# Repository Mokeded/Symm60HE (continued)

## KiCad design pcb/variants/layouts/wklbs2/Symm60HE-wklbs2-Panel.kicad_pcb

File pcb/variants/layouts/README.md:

# Fixed-layout production panels

Each child directory is one self-contained combined electrical project with a
single panel PCB, combined namespaced schematic, captured symbol library and
KiCad project file. Open and manufacture the `*-Panel` project; the retained
`*-Left.kicad_pcb` and `*-Right.kicad_pcb` files are mechanical/migration
inputs rather than separate electrical projects.

The eight directories cover every combination of:

- two 1.5u or three 1u keys on the left bottom row;
- standard or arrow-cluster right bottom row; and
- split or 2u Backspace.

Run `tools/layouts/verify_layout_panels.py` to verify combined schematic/PCB
parity, L/R namespace isolation, FN40HE Hall keepouts, panel dimensions,
mouse-bite rows, tooling holes and fiducials. Matching plate files use the same
directory/layout stem under `plate/`.

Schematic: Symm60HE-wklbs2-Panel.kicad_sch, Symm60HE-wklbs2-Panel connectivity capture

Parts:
L-AML1, L-AML2, L-AML3, L-AML4, L-AML5: SN74LV4051A; AM1_TSSOP-16_4.4x5mm_P0.65mm
L-CL1A, L-CL2A, L-CL3A, L-CL4A, L-CL5A, L-CL6A, L-CL7A, L-CL8A, L-CL9A, L-CL10A, L-CL11A, L-CL12A, L-CL13A, L-CL14A, L-CL15A, L-CL16A, L-CL17A, L-CL18A, L-CL19A, L-CL20A, L-CL21A, L-CL22A, L-CL23A, L-CL24A, L-CL25A, L-CL26A, L-CL28A, L-CL30A, L-CL32A, L-CL33A: 100n; C1_C_0402_1005Metric
L-CL1B, L-CL2B, L-CL3B, L-CL4B, L-CL5B, L-CL6B, L-CL7B, L-CL8B, L-CL9B, L-CL10B, L-CL11B, L-CL12B, L-CL13B, L-CL14B, L-CL15B, L-CL16B, L-CL17B, L-CL18B, L-CL19B, L-CL20B, L-CL21B, L-CL22B, L-CL23B, L-CL24B, L-CL25B, L-CL26B, L-CL28B, L-CL30B, L-CL32B, L-CL33B: 4.7n; C1_C_0402_1005Metric
L-CML1, L-CML2, L-CML3, L-CML4, L-CML5: 100n; C1_C_0402_1005Metric
L-CRGBL1, L-CRGBL2, L-CRGBL3, L-CRGBL4, L-CRGBL5, L-CRGBL6, L-CRGBL7, L-CRGBL8, L-CRGBL9, L-CRGBL10, L-CRGBL11, L-CRGBL12, L-CRGBL13, L-CRGBL14, L-CRGBL15, L-CRGBL16, L-CRGBL17, L-CRGBL18, L-CRGBL19, L-CRGBL20, L-CRGBL21, L-CRGBL22, L-CRGBL23, L-CRGBL24, L-CRGBL25, L-CRGBL26, L-CRGBL27, L-CRGBL29, L-CRGBL30, L-CRGBL31: 100n; C1_C_0402_1005Metric
L-DL1, L-DL2, L-DL3, L-DL4, L-DL5, L-DL6, L-DL7, L-DL8, L-DL9, L-DL10, L-DL11, L-DL12, L-DL13, L-DL14, L-DL15, L-DL16, L-DL17, L-DL18, L-DL19, L-DL20, L-DL21, L-DL22, L-DL23, L-DL24, L-DL25, L-DL26, L-DL27, L-DL29, L-DL30, L-DL31: SK6812MINI-E; SK6812MINI-E_ReverseMount
L-HEL1, L-HEL2, L-HEL3, L-HEL4, L-HEL5, L-HEL6, L-HEL7, L-HEL9, L-HEL10, L-HEL11, L-HEL12, L-HEL13, L-HEL14, L-HEL16, L-HEL17, L-HEL18, L-HEL19, L-HEL20, L-HEL22, L-HEL23, L-HEL24, L-HEL25, L-HEL26: MT9102ET; HE_KEY_1.00u
L-HEL8, L-HEL28, L-HEL30, L-HEL32: MT9102ET; HE_KEY_1.50u
L-HEL15: MT9102ET; HE_KEY_1.75u
L-HEL21, L-HEL33: MT9102ET; HE_KEY_2.25u
L-JL1: FFC_12P; FFC_12P_1.00mm_TopContact
L-RBPL29: 0R_DNP; R3_R_0402_1005Metric_DNP
R-AMR1, R-AMR2, R-AMR3, R-AMR4, R-AMR5: SN74LV4051A; AM1_TSSOP-16_4.4x5mm_P0.65mm
R-CMR1, R-CMR2, R-CMR3, R-CMR4, R-CMR5: 100n; C1_C_0402_1005Metric
R-CR1A, R-CR2A, R-CR4A, R-CR6A, R-CR7A, R-CR8A, R-CR9A, R-CR10A, R-CR11A, R-CR12A, R-CR13A, R-CR14A, R-CR15A, R-CR16A, R-CR17A, R-CR18A, R-CR19A, R-CR20A, R-CR21A, R-CR22A, R-CR23A, R-CR25A, R-CR27A, R-CR28A, R-CR29A, R-CR31A, R-CR33A, R-CR35A, R-CR36A: 100n; C1_C_0402_1005Metric
R-CR1B, R-CR2B, R-CR4B, R-CR6B, R-CR7B, R-CR8B, R-CR9B, R-CR10B, R-CR11B, R-CR12B, R-CR13B, R-CR14B, R-CR15B, R-CR16B, R-CR17B, R-CR18B, R-CR19B, R-CR20B, R-CR21B, R-CR22B, R-CR23B, R-CR25B, R-CR27B, R-CR28B, R-CR29B, R-CR31B, R-CR33B, R-CR35B, R-CR36B: 4.7n; C1_C_0402_1005Metric
R-CRGBR1, R-CRGBR2, R-CRGBR3, R-CRGBR6, R-CRGBR7, R-CRGBR8, R-CRGBR9, R-CRGBR10, R-CRGBR11, R-CRGBR12, R-CRGBR13, R-CRGBR14, R-CRGBR15, R-CRGBR16, R-CRGBR17, R-CRGBR18, R-CRGBR19, R-CRGBR20, R-CRGBR21, R-CRGBR23, R-CRGBR24, R-CRGBR25, R-CRGBR26, R-CRGBR27, R-CRGBR28, R-CRGBR29, R-CRGBR31, R-CRGBR32, R-CRGBR33: 100n; C1_C_0402_1005Metric
R-DR1, R-DR2, R-DR3, R-DR6, R-DR7, R-DR8, R-DR9, R-DR10, R-DR11, R-DR12, R-DR13, R-DR14, R-DR15, R-DR16, R-DR17, R-DR18, R-DR19, R-DR20, R-DR21, R-DR23, R-DR24, R-DR25, R-DR26, R-DR27, R-DR28, R-DR29, R-DR31, R-DR32, R-DR33: SK6812MINI-E; SK6812MINI-E_ReverseMount
R-HER1, R-HER2, R-HER6, R-HER7, R-HER8, R-HER9, R-HER10, R-HER12, R-HER13, R-HER14, R-HER15, R-HER16, R-HER17, R-HER19, R-HER20, R-HER21, R-HER22, R-HER23, R-HER27, R-HER28, R-HER29: MT9102ET; HE_KEY_1.00u
R-HER4: MT9102ET; HE_KEY_2.00u
R-HER11, R-HER31, R-HER33, R-HER35: MT9102ET; HE_KEY_1.50u
R-HER18: MT9102ET; HE_KEY_1.75u
R-HER25, R-HER36: MT9102ET; HE_KEY_2.25u
R-JR1: FFC_12P; FFC_12P_1.00mm_TopContact
R-RBPR5, R-RBPR24, R-RBPR31: 0R_DNP; R3_R_0402_1005Metric_DNP

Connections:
/L/+3V3A: L-AML1.16 (/L/+3V3A), L-AML2.16 (/L/+3V3A), L-AML3.16 (/L/+3V3A), L-AML4.16 (/L/+3V3A), L-AML5.16 (/L/+3V3A), L-CL1A.1 (/L/+3V3A), L-CL2A.1 (/L/+3V3A), L-CL3A.1 (/L/+3V3A), L-CL4A.1 (/L/+3V3A), L-CL5A.1 (/L/+3V3A), L-CL6A.1 (/L/+3V3A), L-CL7A.1 (/L/+3V3A), L-CL8A.1 (/L/+3V3A), L-CL9A.1 (/L/+3V3A), L-CL10A.1 (/L/+3V3A), L-CL11A.1 (/L/+3V3A), L-CL12A.1 (/L/+3V3A), L-CL13A.1 (/L/+3V3A), L-CL14A.1 (/L/+3V3A), L-CL15A.1 (/L/+3V3A), L-CL16A.1 (/L/+3V3A), L-CL17A.1 (/L/+3V3A), L-CL18A.1 (/L/+3V3A), L-CL19A.1 (/L/+3V3A), L-CL20A.1 (/L/+3V3A), L-CL21A.1 (/L/+3V3A), L-CL22A.1 (/L/+3V3A), L-CL23A.1 (/L/+3V3A), L-CL24A.1 (/L/+3V3A), L-CL25A.1 (/L/+3V3A), L-CL26A.1 (/L/+3V3A), L-CL28A.1 (/L/+3V3A), L-CL30A.1 (/L/+3V3A), L-CL32A.1 (/L/+3V3A), L-CL33A.1 (/L/+3V3A), L-CML1.1 (/L/+3V3A), L-CML2.1 (/L/+3V3A), L-CML3.1 (/L/+3V3A), L-CML4.1 (/L/+3V3A), L-CML5.1 (/L/+3V3A), L-HEL1.1 (/L/+3V3A), L-HEL2.1 (/L/+3V3A), L-HEL3.1 (/L/+3V3A), L-HEL4.1 (/L/+3V3A), L-HEL5.1 (/L/+3V3A), L-HEL6.1 (/L/+3V3A), L-HEL7.1 (/L/+3V3A), L-HEL8.1 (/L/+3V3A), L-HEL9.1 (/L/+3V3A), L-HEL10.1 (/L/+3V3A), L-HEL11.1 (/L/+3V3A), L-HEL12.1 (/L/+3V3A), L-HEL13.1 (/L/+3V3A), L-HEL14.1 (/L/+3V3A), L-HEL15.1 (/L/+3V3A), L-HEL16.1 (/L/+3V3A), L-HEL17.1 (/L/+3V3A), L-HEL18.1 (/L/+3V3A), L-HEL19.1 (/L/+3V3A), L-HEL20.1 (/L/+3V3A), L-HEL21.1 (/L/+3V3A), L-HEL22.1 (/L/+3V3A), L-HEL23.1 (/L/+3V3A), L-HEL24.1 (/L/+3V3A), L-HEL25.1 (/L/+3V3A), L-HEL26.1 (/L/+3V3A), L-HEL28.1 (/L/+3V3A), L-HEL30.1 (/L/+3V3A), L-HEL32.1 (/L/+3V3A), L-HEL33.1 (/L/+3V3A), L-JL1.12 (/L/+3V3A)
/L/ADC_L1: L-AML1.3 (/L/ADC_L1), L-JL1.6 (/L/ADC_L1)
/L/ADC_L2: L-AML2.3 (/L/ADC_L2), L-JL1.4 (/L/ADC_L2)
/L/ADC_L3: L-AML3.3 (/L/ADC_L3), L-JL1.2 (/L/ADC_L3)
/L/ADC_L4: L-AML4.3 (/L/ADC_L4), L-JL1.1 (/L/ADC_L4)
/L/ADC_L5: L-AML5.3 (/L/ADC_L5), L-JL1.11 (/L/ADC_L5)
/L/GND: L-AML1.6 (/L/GND), L-AML1.7 (/L/GND), L-AML1.8 (/L/GND), L-AML2.4 (/L/GND), L-AML2.6 (/L/GND), L-AML2.7 (/L/GND), L-AML2.8 (/L/GND), L-AML3.6 (/L/GND), L-AML3.7 (/L/GND), L-AML3.8 (/L/GND), L-AML4.2 (/L/GND), L-AML4.4 (/L/GND), L-AML4.6 (/L/GND), L-AML4.7 (/L/GND), L-AML4.8 (/L/GND), L-AML4.13 (/L/GND), L-AML4.14 (/L/GND), L-AML5.6 (/L/GND), L-AML5.7 (/L/GND), L-AML5.8 (/L/GND), L-AML5.12 (/L/GND), L-AML5.13 (/L/GND), L-AML5.14 (/L/GND), L-AML5.15 (/L/GND), L-CL1A.2 (/L/GND), L-CL1B.2 (/L/GND), L-CL2A.2 (/L/GND), L-CL2B.2 (/L/GND), L-CL3A.2 (/L/GND), L-CL3B.2 (/L/GND), L-CL4A.2 (/L/GND), L-CL4B.2 (/L/GND), L-CL5A.2 (/L/GND), L-CL5B.2 (/L/GND), L-CL6A.2 (/L/GND), L-CL6B.2 (/L/GND), L-CL7A.2 (/L/GND), L-CL7B.2 (/L/GND), L-CL8A.2 (/L/GND), L-CL8B.2 (/L/GND), L-CL9A.2 (/L/GND), L-CL9B.2 (/L/GND), L-CL10A.2 (/L/GND), L-CL10B.2 (/L/GND), L-CL11A.2 (/L/GND), L-CL11B.2 (/L/GND), L-CL12A.2 (/L/GND), L-CL12B.2 (/L/GND), L-CL13A.2 (/L/GND), L-CL13B.2 (/L/GND), L-CL14A.2 (/L/GND), L-CL14B.2 (/L/GND), L-CL15A.2 (/L/GND), L-CL15B.2 (/L/GND), L-CL16A.2 (/L/GND), L-CL16B.2 (/L/GND), L-CL17A.2 (/L/GND), L-CL17B.2 (/L/GND), L-CL18A.2 (/L/GND), L-CL18B.2 (/L/GND), L-CL19A.2 (/L/GND), L-CL19B.2 (/L/GND), L-CL20A.2 (/L/GND), L-CL20B.2 (/L/GND), L-CL21A.2 (/L/GND), L-CL21B.2 (/L/GND), L-CL22A.2 (/L/GND), L-CL22B.2 (/L/GND), L-CL23A.2 (/L/GND), L-CL23B.2 (/L/GND), L-CL24A.2 (/L/GND), L-CL24B.2 (/L/GND), L-CL25A.2 (/L/GND), L-CL25B.2 (/L/GND), L-CL26A.2 (/L/GND), L-CL26B.2 (/L/GND), L-CL28A.2 (/L/GND), L-CL28B.2 (/L/GND), L-CL30A.2 (/L/GND), L-CL30B.2 (/L/GND), L-CL32A.2 (/L/GND), L-CL32B.2 (/L/GND), L-CL33A.2 (/L/GND), L-CL33B.2 (/L/GND), L-CML1.2 (/L/GND), L-CML2.2 (/L/GND), L-CML3.2 (/L/GND), L-CML4.2 (/L/GND), L-CML5.2 (/L/GND), L-CRGBL1.2 (/L/GND), L-CRGBL2.2 (/L/GND), L-CRGBL3.2 (/L/GND), L-CRGBL4.2 (/L/GND), L-CRGBL5.2 (/L/GND), L-CRGBL6.2 (/L/GND), L-CRGBL7.2 (/L/GND), L-CRGBL8.2 (/L/GND), L-CRGBL9.2 (/L/GND), L-CRGBL10.2 (/L/GND), L-CRGBL11.2 (/L/GND), L-CRGBL12.2 (/L/GND), L-CRGBL13.2 (/L/GND)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
/L/HE_L01: L-AML1.12 (/L/HE_L01), L-CL1B.1 (/L/HE_L01), L-HEL1.3 (/L/HE_L01)
/L/HE_L02: L-AML1.13 (/L/HE_L02), L-CL2B.1 (/L/HE_L02), L-HEL2.3 (/L/HE_L02)
/L/HE_L03: L-AML1.14 (/L/HE_L03), L-CL3B.1 (/L/HE_L03), L-HEL3.3 (/L/HE_L03)
/L/HE_L04: L-AML1.15 (/L/HE_L04), L-CL4B.1 (/L/HE_L04), L-HEL4.3 (/L/HE_L04)
/L/HE_L05: L-AML2.12 (/L/HE_L05), L-CL5B.1 (/L/HE_L05), L-HEL5.3 (/L/HE_L05)
/L/HE_L06: L-AML2.13 (/L/HE_L06), L-CL6B.1 (/L/HE_L06), L-HEL6.3 (/L/HE_L06)
/L/HE_L07: L-AML2.14 (/L/HE_L07), L-CL7B.1 (/L/HE_L07), L-HEL7.3 (/L/HE_L07)
/L/HE_L08: L-AML1.5 (/L/HE_L08), L-CL8B.1 (/L/HE_L08), L-HEL8.3 (/L/HE_L08)
/L/HE_L09: L-AML1.4 (/L/HE_L09), L-CL9B.1 (/L/HE_L09), L-HEL9.3 (/L/HE_L09)
/L/HE_L10: L-AML1.2 (/L/HE_L10), L-CL10B.1 (/L/HE_L10), L-HEL10.3 (/L/HE_L10)
/L/HE_L11: L-AML1.1 (/L/HE_L11), L-CL11B.1 (/L/HE_L11), L-HEL11.3 (/L/HE_L11)
/L/HE_L12: L-AML2.5 (/L/HE_L12), L-CL12B.1 (/L/HE_L12), L-HEL12.3 (/L/HE_L12)
/L/HE_L13: L-AML2.2 (/L/HE_L13), L-CL13B.1 (/L/HE_L13), L-HEL13.3 (/L/HE_L13)
/L/HE_L14: L-AML2.1 (/L/HE_L14), L-CL14B.1 (/L/HE_L14), L-HEL14.3 (/L/HE_L14)
/L/HE_L15: L-AML3.12 (/L/HE_L15), L-CL15B.1 (/L/HE_L15), L-HEL15.3 (/L/HE_L15)
/L/HE_L16: L-AML3.13 (/L/HE_L16), L-CL16B.1 (/L/HE_L16), L-HEL16.3 (/L/HE_L16)
/L/HE_L17: L-AML3.14 (/L/HE_L17), L-CL17B.1 (/L/HE_L17), L-HEL17.3 (/L/HE_L17)
/L/HE_L18: L-AML3.15 (/L/HE_L18), L-CL18B.1 (/L/HE_L18), L-HEL18.3 (/L/HE_L18)
/L/HE_L19: L-AML4.12 (/L/HE_L19), L-CL19B.1 (/L/HE_L19), L-HEL19.3 (/L/HE_L19)
/L/HE_L20: L-AML4.15 (/L/HE_L20), L-CL20B.1 (/L/HE_L20), L-HEL20.3 (/L/HE_L20)
/L/HE_L21: L-AML3.5 (/L/HE_L21), L-CL21B.1 (/L/HE_L21), L-HEL21.3 (/L/HE_L21)
/L/HE_L22: L-AML3.4 (/L/HE_L22), L-CL22B.1 (/L/HE_L22), L-HEL22.3 (/L/HE_L22)
/L/HE_L23: L-AML3.2 (/L/HE_L23), L-CL23B.1 (/L/HE_L23), L-HEL23.3 (/L/HE_L23)
/L/HE_L24: L-AML3.1 (/L/HE_L24), L-CL24B.1 (/L/HE_L24), L-HEL24.3 (/L/HE_L24)
/L/HE_L25: L-AML4.5 (/L/HE_L25), L-CL25B.1 (/L/HE_L25), L-HEL25.3 (/L/HE_L25)
/L/HE_L26: L-AML4.1 (/L/HE_L26), L-CL26B.1 (/L/HE_L26), L-HEL26.3 (/L/HE_L26)
/L/HE_L30: L-AML5.2 (/L/HE_L30), L-CL32B.1 (/L/HE_L30), L-HEL32.3 (/L/HE_L30)
/L/HE_L31: L-AML5.1 (/L/HE_L31), L-CL33B.1 (/L/HE_L31), L-HEL33.3 (/L/HE_L31)
/L/HE_L32: L-AML5.4 (/L/HE_L32), L-CL28B.1 (/L/HE_L32), L-HEL28.3 (/L/HE_L32)
/L/HE_L33: L-AML5.5 (/L/HE_L33), L-CL30B.1 (/L/HE_L33), L-HEL30.3 (/L/HE_L33)
/L/MUX_A0: L-AML1.11 (/L/MUX_A0), L-AML2.11 (/L/MUX_A0), L-AML3.11 (/L/MUX_A0), L-AML4.11 (/L/MUX_A0), L-AML5.11 (/L/MUX_A0), L-JL1.10 (/L/MUX_A0)
/L/MUX_A1: L-AML1.10 (/L/MUX_A1), L-AML2.10 (/L/MUX_A1), L-AML3.10 (/L/MUX_A1), L-AML4.10 (/L/MUX_A1), L-AML5.10 (/L/MUX_A1), L-JL1.9 (/L/MUX_A1)
/L/MUX_A2: L-AML1.9 (/L/MUX_A2), L-AML2.9 (/L/MUX_A2), L-AML3.9 (/L/MUX_A2), L-AML4.9 (/L/MUX_A2), L-AML5.9 (/L/MUX_A2), L-JL1.8 (/L/MUX_A2)
/L/RGB_L: L-DL1.2 (/L/RGB_L), L-JL1.3 (/L/RGB_L)
/L/RGB_L_01: L-DL1.4 (/L/RGB_L_01), L-DL2.2 (/L/RGB_L_01)
/L/RGB_L_02: L-DL2.4 (/L/RGB_L_02), L-DL3.2 (/L/RGB_L_02)
/L/RGB_L_03: L-DL3.4 (/L/RGB_L_03), L-DL4.2 (/L/RGB_L_03)
/L/RGB_L_04: L-DL4.4 (/L/RGB_L_04), L-DL5.2 (/L/RGB_L_04)
/L/RGB_L_05: L-DL5.4 (/L/RGB_L_05), L-DL6.2 (/L/RGB_L_05)
/L/RGB_L_06: L-DL6.4 (/L/RGB_L_06), L-DL7.2 (/L/RGB_L_06)
/L/RGB_L_07: L-DL7.4 (/L/RGB_L_07), L-DL8.2 (/L/RGB_L_07)
/L/RGB_L_08: L-DL8.4 (/L/RGB_L_08), L-DL9.2 (/L/RGB_L_08)
/L/RGB_L_09: L-DL9.4 (/L/RGB_L_09), L-DL10.2 (/L/RGB_L_09)
/L/RGB_L_10: L-DL10.4 (/L/RGB_L_10), L-DL11.2 (/L/RGB_L_10)
/L/RGB_L_11: L-DL11.4 (/L/RGB_L_11), L-DL12.2 (/L/RGB_L_11)
/L/RGB_L_12: L-DL12.4 (/L/RGB_L_12), L-DL13.2 (/L/RGB_L_12)
/L/RGB_L_13: L-DL13.4 (/L/RGB_L_13), L-DL14.2 (/L/RGB_L_13)
/L/RGB_L_14: L-DL14.4 (/L/RGB_L_14), L-DL15.2 (/L/RGB_L_14)
/L/RGB_L_15: L-DL15.4 (/L/RGB_L_15), L-DL16.2 (/L/RGB_L_15)
/L/RGB_L_16: L-DL16.4 (/L/RGB_L_16), L-DL17.2 (/L/RGB_L_16)
/L/RGB_L_17: L-DL17.4 (/L/RGB_L_17), L-DL18.2 (/L/RGB_L_17)
/L/RGB_L_18: L-DL18.4 (/L/RGB_L_18), L-DL19.2 (/L/RGB_L_18)
/L/RGB_L_19: L-DL19.4 (/L/RGB_L_19), L-DL20.2 (/L/RGB_L_19)
/L/RGB_L_20: L-DL20.4 (/L/RGB_L_20), L-DL21.2 (/L/RGB_L_20)
/L/RGB_L_21: L-DL21.4 (/L/RGB_L_21), L-DL22.2 (/L/RGB_L_21)
/L/RGB_L_22: L-DL22.4 (/L/RGB_L_22), L-DL23.2 (/L/RGB_L_22)
/L/RGB_L_23: L-DL23.4 (/L/RGB_L_23), L-DL24.2 (/L/RGB_L_23)
/L/RGB_L_24: L-DL24.4 (/L/RGB_L_24), L-DL25.2 (/L/RGB_L_24)
/L/RGB_L_25: L-DL25.4 (/L/RGB_L_25), L-DL26.2 (/L/RGB_L_25)
/L/RGB_L_26: L-DL26.4 (/L/RGB_L_26), L-DL27.2 (/L/RGB_L_26)
/L/RGB_L_27: L-DL27.4 (/L/RGB_L_27), L-DL29.2 (/L/RGB_L_27), L-RBPL29.1 (/L/RGB_L_27)
/L/RGB_L_29: L-DL29.4 (/L/RGB_L_29), L-DL30.2 (/L/RGB_L_29), L-RBPL29.2 (/L/RGB_L_29)
/L/RGB_L_30: L-DL30.4 (/L/RGB_L_30), L-DL31.2 (/L/RGB_L_30)
/L/RGB_L_END: L-DL31.4 (/L/RGB_L_END)
/L/VBUS: L-CRGBL1.1 (/L/VBUS), L-CRGBL2.1 (/L/VBUS), L-CRGBL3.1 (/L/VBUS), L-CRGBL4.1 (/L/VBUS), L-CRGBL5.1 (/L/VBUS), L-CRGBL6.1 (/L/VBUS), L-CRGBL7.1 (/L/VBUS), L-CRGBL8.1 (/L/VBUS), L-CRGBL9.1 (/L/VBUS), L-CRGBL10.1 (/L/VBUS), L-CRGBL11.1 (/L/VBUS), L-CRGBL12.1 (/L/VBUS), L-CRGBL13.1 (/L/VBUS), L-CRGBL14.1 (/L/VBUS), L-CRGBL15.1 (/L/VBUS), L-CRGBL16.1 (/L/VBUS), L-CRGBL17.1 (/L/VBUS), L-CRGBL18.1 (/L/VBUS), L-CRGBL19.1 (/L/VBUS), L-CRGBL20.1 (/L/VBUS), L-CRGBL21.1 (/L/VBUS), L-CRGBL22.1 (/L/VBUS), L-CRGBL23.1 (/L/VBUS), L-CRGBL24.1 (/L/VBUS), L-CRGBL25.1 (/L/VBUS), L-CRGBL26.1 (/L/VBUS), L-CRGBL27.1 (/L/VBUS), L-CRGBL29.1 (/L/VBUS), L-CRGBL30.1 (/L/VBUS), L-CRGBL31.1 (/L/VBUS), L-DL1.3 (/L/VBUS), L-DL2.3 (/L/VBUS), L-DL3.3 (/L/VBUS), L-DL4.3 (/L/VBUS), L-DL5.3 (/L/VBUS), L-DL6.3 (/L/VBUS), L-DL7.3 (/L/VBUS), L-DL8.3 (/L/VBUS), L-DL9.3 (/L/VBUS), L-DL10.3 (/L/VBUS), L-DL11.3 (/L/VBUS), L-DL12.3 (/L/VBUS), L-DL13.3 (/L/VBUS), L-DL14.3 (/L/VBUS), L-DL15.3 (/L/VBUS), L-DL16.3 (/L/VBUS), L-DL17.3 (/L/VBUS), L-DL18.3 (/L/VBUS), L-DL19.3 (/L/VBUS), L-DL20.3 (/L/VBUS), L-DL21.3 (/L/VBUS), L-DL22.3 (/L/VBUS), L-DL23.3 (/L/VBUS), L-DL24.3 (/L/VBUS), L-DL25.3 (/L/VBUS), L-DL26.3 (/L/VBUS), L-DL27.3 (/L/VBUS), L-DL29.3 (/L/VBUS), L-DL30.3 (/L/VBUS), L-DL31.3 (/L/VBUS), L-JL1.7 (/L/VBUS)
/R/+3V3A: R-AMR1.16 (/R/+3V3A), R-AMR2.16 (/R/+3V3A), R-AMR3.16 (/R/+3V3A), R-AMR4.16 (/R/+3V3A), R-AMR5.16 (/R/+3V3A), R-CMR1.1 (/R/+3V3A), R-CMR2.1 (/R/+3V3A), R-CMR3.1 (/R/+3V3A), R-CMR4.1 (/R/+3V3A), R-CMR5.1 (/R/+3V3A), R-CR1A.1 (/R/+3V3A), R-CR2A.1 (/R/+3V3A), R-CR4A.1 (/R/+3V3A), R-CR6A.1 (/R/+3V3A), R-CR7A.1 (/R/+3V3A), R-CR8A.1 (/R/+3V3A), R-CR9A.1 (/R/+3V3A), R-CR10A.1 (/R/+3V3A), R-CR11A.1 (/R/+3V3A), R-CR12A.1 (/R/+3V3A), R-CR13A.1 (/R/+3V3A), R-CR14A.1 (/R/+3V3A), R-CR15A.1 (/R/+3V3A), R-CR16A.1 (/R/+3V3A), R-CR17A.1 (/R/+3V3A), R-CR18A.1 (/R/+3V3A), R-CR19A.1 (/R/+3V3A), R-CR20A.1 (/R/+3V3A), R-CR21A.1 (/R/+3V3A), R-CR22A.1 (/R/+3V3A), R-CR23A.1 (/R/+3V3A), R-CR25A.1 (/R/+3V3A), R-CR27A.1 (/R/+3V3A), R-CR28A.1 (/R/+3V3A), R-CR29A.1 (/R/+3V3A), R-CR31A.1 (/R/+3V3A), R-CR33A.1 (/R/+3V3A), R-CR35A.1 (/R/+3V3A), R-CR36A.1 (/R/+3V3A), R-HER1.1 (/R/+3V3A), R-HER2.1 (/R/+3V3A), R-HER4.1 (/R/+3V3A), R-HER6.1 (/R/+3V3A), R-HER7.1 (/R/+3V3A), R-HER8.1 (/R/+3V3A), R-HER9.1 (/R/+3V3A), R-HER10.1 (/R/+3V3A), R-HER11.1 (/R/+3V3A), R-HER12.1 (/R/+3V3A), R-HER13.1 (/R/+3V3A), R-HER14.1 (/R/+3V3A), R-HER15.1 (/R/+3V3A), R-HER16.1 (/R/+3V3A), R-HER17.1 (/R/+3V3A), R-HER18.1 (/R/+3V3A), R-HER19.1 (/R/+3V3A), R-HER20.1 (/R/+3V3A), R-HER21.1 (/R/+3V3A), R-HER22.1 (/R/+3V3A), R-HER23.1 (/R/+3V3A), R-HER25.1 (/R/+3V3A), R-HER27.1 (/R/+3V3A), R-HER28.1 (/R/+3V3A), R-HER29.1 (/R/+3V3A), R-HER31.1 (/R/+3V3A), R-HER33.1 (/R/+3V3A), R-HER35.1 (/R/+3V3A), R-HER36.1 (/R/+3V3A), R-JR1.1 (/R/+3V3A)
/R/ADC_R1: R-AMR1.3 (/R/ADC_R1), R-JR1.7 (/R/ADC_R1)
/R/ADC_R2: R-AMR2.3 (/R/ADC_R2), R-JR1.9 (/R/ADC_R2)
/R/ADC_R3: R-AMR3.3 (/R/ADC_R3), R-JR1.11 (/R/ADC_R3)
/R/ADC_R4: R-AMR4.3 (/R/ADC_R4), R-JR1.12 (/R/ADC_R4)
/R/ADC_R5: R-AMR5.3 (/R/ADC_R5), R-JR1.2 (/R/ADC_R5)
/R/GND: R-AMR1.6 (/R/GND), R-AMR1.7 (/R/GND), R-AMR1.8 (/R/GND), R-AMR1.15 (/R/GND), R-AMR2.1 (/R/GND), R-AMR2.6 (/R/GND), R-AMR2.7 (/R/GND), R-AMR2.8 (/R/GND), R-AMR2.15 (/R/GND), R-AMR3.6 (/R/GND), R-AMR3.7 (/R/GND), R-AMR3.8 (/R/GND), R-AMR4.1 (/R/GND), R-AMR4.2 (/R/GND), R-AMR4.6 (/R/GND), R-AMR4.7 (/R/GND), R-AMR4.8 (/R/GND), R-AMR4.14 (/R/GND), R-AMR4.15 (/R/GND), R-AMR5.6 (/R/GND), R-AMR5.7 (/R/GND), R-AMR5.8 (/R/GND), R-AMR5.12 (/R/GND), R-AMR5.13 (/R/GND), R-AMR5.14 (/R/GND), R-AMR5.15 (/R/GND), R-CMR1.2 (/R/GND), R-CMR2.2 (/R/GND), R-CMR3.2 (/R/GND), R-CMR4.2 (/R/GND), R-CMR5.2 (/R/GND), R-CR1A.2 (/R/GND), R-CR1B.2 (/R/GND), R-CR2A.2 (/R/GND), R-CR2B.2 (/R/GND), R-CR4A.2 (/R/GND), R-CR4B.2 (/R/GND), R-CR6A.2 (/R/GND), R-CR6B.2 (/R/GND), R-CR7A.2 (/R/GND), R-CR7B.2 (/R/GND), R-CR8A.2 (/R/GND), R-CR8B.2 (/R/GND), R-CR9A.2 (/R/GND), R-CR9B.2 (/R/GND), R-CR10A.2 (/R/GND), R-CR10B.2 (/R/GND), R-CR11A.2 (/R/GND), R-CR11B.2 (/R/GND), R-CR12A.2 (/R/GND), R-CR12B.2 (/R/GND), R-CR13A.2 (/R/GND), R-CR13B.2 (/R/GND), R-CR14A.2 (/R/GND), R-CR14B.2 (/R/GND), R-CR15A.2 (/R/GND), R-CR15B.2 (/R/GND), R-CR16A.2 (/R/GND), R-CR16B.2 (/R/GND), R-CR17A.2 (/R/GND), R-CR17B.2 (/R/GND), R-CR18A.2 (/R/GND), R-CR18B.2 (/R/GND), R-CR19A.2 (/R/GND), R-CR19B.2 (/R/GND), R-CR20A.2 (/R/GND), R-CR20B.2 (/R/GND), R-CR21A.2 (/R/GND), R-CR21B.2 (/R/GND), R-CR22A.2 (/R/GND), R-CR22B.2 (/R/GND), R-CR23A.2 (/R/GND), R-CR23B.2 (/R/GND), R-CR25A.2 (/R/GND), R-CR25B.2 (/R/GND), R-CR27A.2 (/R/GND), R-CR27B.2 (/R/GND), R-CR28A.2 (/R/GND), R-CR28B.2 (/R/GND), R-CR29A.2 (/R/GND), R-CR29B.2 (/R/GND), R-CR31A.2 (/R/GND), R-CR31B.2 (/R/GND), R-CR33A.2 (/R/GND), R-CR33B.2 (/R/GND), R-CR35A.2 (/R/GND), R-CR35B.2 (/R/GND), R-CR36A.2 (/R/GND), R-CR36B.2 (/R/GND), R-CRGBR1.2 (/R/GND), R-CRGBR2.2 (/R/GND), R-CRGBR3.2 (/R/GND), R-CRGBR6.2 (/R/GND), R-CRGBR7.2 (/R/GND), R-CRGBR8.2 (/R/GND), R-CRGBR9.2 (/R/GND), R-CRGBR10.2 (/R/GND), R-CRGBR11.2 (/R/GND), R-CRGBR12.2 (/R/GND), R-CRGBR13.2 (/R/GND), R-CRGBR14.2 (/R/GND), R-CRGBR15.2 (/R/GND)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
/R/HE_R01: R-AMR2.14 (/R/HE_R01), R-CR6B.1 (/R/HE_R01), R-HER6.3 (/R/HE_R01)
/R/HE_R02: R-AMR1.12 (/R/HE_R02), R-CR1B.1 (/R/HE_R02), R-HER1.3 (/R/HE_R02)
/R/HE_R03: R-AMR1.13 (/R/HE_R03), R-CR2B.1 (/R/HE_R03), R-HER2.3 (/R/HE_R03)
/R/HE_R04: R-AMR1.14 (/R/HE_R04), R-CR4B.1 (/R/HE_R04), R-HER4.3 (/R/HE_R04)
/R/HE_R06: R-AMR2.13 (/R/HE_R06), R-CR7B.1 (/R/HE_R06), R-HER7.3 (/R/HE_R06)
/R/HE_R07: R-AMR2.12 (/R/HE_R07), R-CR8B.1 (/R/HE_R07), R-HER8.3 (/R/HE_R07)
/R/HE_R08: R-AMR2.2 (/R/HE_R08), R-CR13B.1 (/R/HE_R08), R-HER13.3 (/R/HE_R08)
/R/HE_R09: R-AMR1.5 (/R/HE_R09), R-CR12B.1 (/R/HE_R09), R-HER12.3 (/R/HE_R09)
/R/HE_R10: R-AMR1.4 (/R/HE_R10), R-CR9B.1 (/R/HE_R10), R-HER9.3 (/R/HE_R10)
/R/HE_R11: R-AMR1.2 (/R/HE_R11), R-CR10B.1 (/R/HE_R11), R-HER10.3 (/R/HE_R11)
/R/HE_R12: R-AMR1.1 (/R/HE_R12), R-CR11B.1 (/R/HE_R12), R-HER11.3 (/R/HE_R12)
/R/HE_R13: R-AMR2.4 (/R/HE_R13), R-CR14B.1 (/R/HE_R13), R-HER14.3 (/R/HE_R13)
/R/HE_R14: R-AMR2.5 (/R/HE_R14), R-CR15B.1 (/R/HE_R14), R-HER15.3 (/R/HE_R14)
/R/HE_R15: R-AMR3.12 (/R/HE_R15), R-CR19B.1 (/R/HE_R15), R-HER19.3 (/R/HE_R15)
/R/HE_R16: R-AMR3.13 (/R/HE_R16), R-CR16B.1 (/R/HE_R16), R-HER16.3 (/R/HE_R16)
/R/HE_R17: R-AMR3.14 (/R/HE_R17), R-CR17B.1 (/R/HE_R17), R-HER17.3 (/R/HE_R17)
/R/HE_R18: R-AMR3.15 (/R/HE_R18), R-CR18B.1 (/R/HE_R18), R-HER18.3 (/R/HE_R18)
/R/HE_R19: R-AMR4.13 (/R/HE_R19), R-CR20B.1 (/R/HE_R19), R-HER20.3 (/R/HE_R19)
/R/HE_R20: R-AMR4.12 (/R/HE_R20), R-CR21B.1 (/R/HE_R20), R-HER21.3 (/R/HE_R20)
/R/HE_R21: R-AMR3.5 (/R/HE_R21), R-CR27B.1 (/R/HE_R21), R-HER27.3 (/R/HE_R21)
/R/HE_R22: R-AMR3.4 (/R/HE_R22), R-CR22B.1 (/R/HE_R22), R-HER22.3 (/R/HE_R22)
/R/HE_R23: R-AMR3.2 (/R/HE_R23), R-CR23B.1 (/R/HE_R23), R-HER23.3 (/R/HE_R23)
/R/HE_R25: R-AMR3.1 (/R/HE_R25), R-CR25B.1 (/R/HE_R25), R-HER25.3 (/R/HE_R25)
/R/HE_R26: R-AMR4.4 (/R/HE_R26), R-CR28B.1 (/R/HE_R26), R-HER28.3 (/R/HE_R26)
/R/HE_R27: R-AMR4.5 (/R/HE_R27), R-CR29B.1 (/R/HE_R27), R-HER29.3 (/R/HE_R27)
/R/HE_R28: R-AMR5.4 (/R/HE_R28), R-CR35B.1 (/R/HE_R28), R-HER35.3 (/R/HE_R28)
/R/HE_R32: R-AMR5.5 (/R/HE_R32), R-CR36B.1 (/R/HE_R32), R-HER36.3 (/R/HE_R32)
/R/HE_R35: R-AMR5.2 (/R/HE_R35), R-CR31B.1 (/R/HE_R35), R-HER31.3 (/R/HE_R35)
/R/HE_R36: R-AMR5.1 (/R/HE_R36), R-CR33B.1 (/R/HE_R36), R-HER33.3 (/R/HE_R36)
/R/MUX_A0: R-AMR1.11 (/R/MUX_A0), R-AMR2.11 (/R/MUX_A0), R-AMR3.11 (/R/MUX_A0), R-AMR4.11 (/R/MUX_A0), R-AMR5.11 (/R/MUX_A0), R-JR1.3 (/R/MUX_A0)
/R/MUX_A1: R-AMR1.10 (/R/MUX_A1), R-AMR2.10 (/R/MUX_A1), R-AMR3.10 (/R/MUX_A1), R-AMR4.10 (/R/MUX_A1), R-AMR5.10 (/R/MUX_A1), R-JR1.4 (/R/MUX_A1)
/R/MUX_A2: R-AMR1.9 (/R/MUX_A2), R-AMR2.9 (/R/MUX_A2), R-AMR3.9 (/R/MUX_A2), R-AMR4.9 (/R/MUX_A2), R-AMR5.9 (/R/MUX_A2), R-JR1.5 (/R/MUX_A2)
/R/RGB_R: R-DR1.2 (/R/RGB_R), R-JR1.10 (/R/RGB_R)
/R/RGB_R_01: R-DR1.4 (/R/RGB_R_01), R-DR2.2 (/R/RGB_R_01)
/R/RGB_R_02: R-DR2.4 (/R/RGB_R_02), R-DR3.2 (/R/RGB_R_02)
/R/RGB_R_03: R-DR3.4 (/R/RGB_R_03), R-DR33.2 (/R/RGB_R_03)
/R/RGB_R_04: R-DR33.4 (/R/RGB_R_04), R-RBPR5.1 (/R/RGB_R_04)
/R/RGB_R_05: R-DR6.2 (/R/RGB_R_05), R-RBPR5.2 (/R/RGB_R_05)
/R/RGB_R_06: R-DR6.4 (/R/RGB_R_06), R-DR7.2 (/R/RGB_R_06)
/R/RGB_R_07: R-DR7.4 (/R/RGB_R_07), R-DR8.2 (/R/RGB_R_07)
/R/RGB_R_08: R-DR8.4 (/R/RGB_R_08), R-DR9.2 (/R/RGB_R_08)
/R/RGB_R_09: R-DR9.4 (/R/RGB_R_09), R-DR10.2 (/R/RGB_R_09)
/R/RGB_R_10: R-DR10.4 (/R/RGB_R_10), R-DR11.2 (/R/RGB_R_10)
/R/RGB_R_11: R-DR11.4 (/R/RGB_R_11), R-DR12.2 (/R/RGB_R_11)
/R/RGB_R_12: R-DR12.4 (/R/RGB_R_12), R-DR13.2 (/R/RGB_R_12)
/R/RGB_R_13: R-DR13.4 (/R/RGB_R_13), R-DR14.2 (/R/RGB_R_13)
/R/RGB_R_14: R-DR14.4 (/R/RGB_R_14), R-DR15.2 (/R/RGB_R_14)
/R/RGB_R_15: R-DR15.4 (/R/RGB_R_15), R-DR16.2 (/R/RGB_R_15)
/R/RGB_R_16: R-DR16.4 (/R/RGB_R_16), R-DR17.2 (/R/RGB_R_16)
/R/RGB_R_17: R-DR17.4 (/R/RGB_R_17), R-DR18.2 (/R/RGB_R_17)
/R/RGB_R_18: R-DR18.4 (/R/RGB_R_18), R-DR19.2 (/R/RGB_R_18)
/R/RGB_R_19: R-DR19.4 (/R/RGB_R_19), R-DR20.2 (/R/RGB_R_19)
/R/RGB_R_20: R-DR20.4 (/R/RGB_R_20), R-DR21.2 (/R/RGB_R_20)
/R/RGB_R_21: R-DR21.4 (/R/RGB_R_21)
/R/RGB_R_22: R-DR23.2 (/R/RGB_R_22)
/R/RGB_R_23: R-DR23.4 (/R/RGB_R_23), R-DR24.2 (/R/RGB_R_23), R-RBPR24.1 (/R/RGB_R_23)
/R/RGB_R_24: R-DR24.4 (/R/RGB_R_24), R-DR25.2 (/R/RGB_R_24), R-RBPR24.2 (/R/RGB_R_24)
/R/RGB_R_25: R-DR25.4 (/R/RGB_R_25), R-DR26.2 (/R/RGB_R_25)
/R/RGB_R_26: R-DR26.4 (/R/RGB_R_26), R-DR27.2 (/R/RGB_R_26)
/R/RGB_R_27: R-DR27.4 (/R/RGB_R_27), R-DR28.2 (/R/RGB_R_27)
/R/RGB_R_28: R-DR28.4 (/R/RGB_R_28), R-DR29.2 (/R/RGB_R_28)
/R/RGB_R_29: R-DR29.4 (/R/RGB_R_29), R-DR31.2 (/R/RGB_R_29), R-RBPR31.1 (/R/RGB_R_29)
/R/RGB_R_31: R-DR31.4 (/R/RGB_R_31), R-DR32.2 (/R/RGB_R_31), R-RBPR31.2 (/R/RGB_R_31)
/R/RGB_R_END: R-DR32.4 (/R/RGB_R_END)
/R/VBUS: R-CRGBR1.1 (/R/VBUS), R-CRGBR2.1 (/R/VBUS), R-CRGBR3.1 (/R/VBUS), R-CRGBR6.1 (/R/VBUS), R-CRGBR7.1 (/R/VBUS), R-CRGBR8.1 (/R/VBUS), R-CRGBR9.1 (/R/VBUS), R-CRGBR10.1 (/R/VBUS), R-CRGBR11.1 (/R/VBUS), R-CRGBR12.1 (/R/VBUS), R-CRGBR13.1 (/R/VBUS), R-CRGBR14.1 (/R/VBUS), R-CRGBR15.1 (/R/VBUS), R-CRGBR16.1 (/R/VBUS), R-CRGBR17.1 (/R/VBUS), R-CRGBR18.1 (/R/VBUS), R-CRGBR19.1 (/R/VBUS), R-CRGBR20.1 (/R/VBUS), R-CRGBR21.1 (/R/VBUS), R-CRGBR23.1 (/R/VBUS), R-CRGBR24.1 (/R/VBUS), R-CRGBR25.1 (/R/VBUS), R-CRGBR26.1 (/R/VBUS), R-CRGBR27.1 (/R/VBUS), R-CRGBR28.1 (/R/VBUS), R-CRGBR29.1 (/R/VBUS), R-CRGBR31.1 (/R/VBUS), R-CRGBR32.1 (/R/VBUS), R-CRGBR33.1 (/R/VBUS), R-DR1.3 (/R/VBUS), R-DR2.3 (/R/VBUS), R-DR3.3 (/R/VBUS), R-DR6.3 (/R/VBUS), R-DR7.3 (/R/VBUS), R-DR8.3 (/R/VBUS), R-DR9.3 (/R/VBUS), R-DR10.3 (/R/VBUS), R-DR11.3 (/R/VBUS), R-DR12.3 (/R/VBUS), R-DR13.3 (/R/VBUS), R-DR14.3 (/R/VBUS), R-DR15.3 (/R/VBUS), R-DR16.3 (/R/VBUS), R-DR17.3 (/R/VBUS), R-DR18.3 (/R/VBUS), R-DR19.3 (/R/VBUS), R-DR20.3 (/R/VBUS), R-DR21.3 (/R/VBUS), R-DR23.3 (/R/VBUS), R-DR24.3 (/R/VBUS), R-DR25.3 (/R/VBUS), R-DR26.3 (/R/VBUS), R-DR27.3 (/R/VBUS), R-DR28.3 (/R/VBUS), R-DR29.3 (/R/VBUS), R-DR31.3 (/R/VBUS), R-DR32.3 (/R/VBUS), R-DR33.3 (/R/VBUS), R-JR1.6 (/R/VBUS)

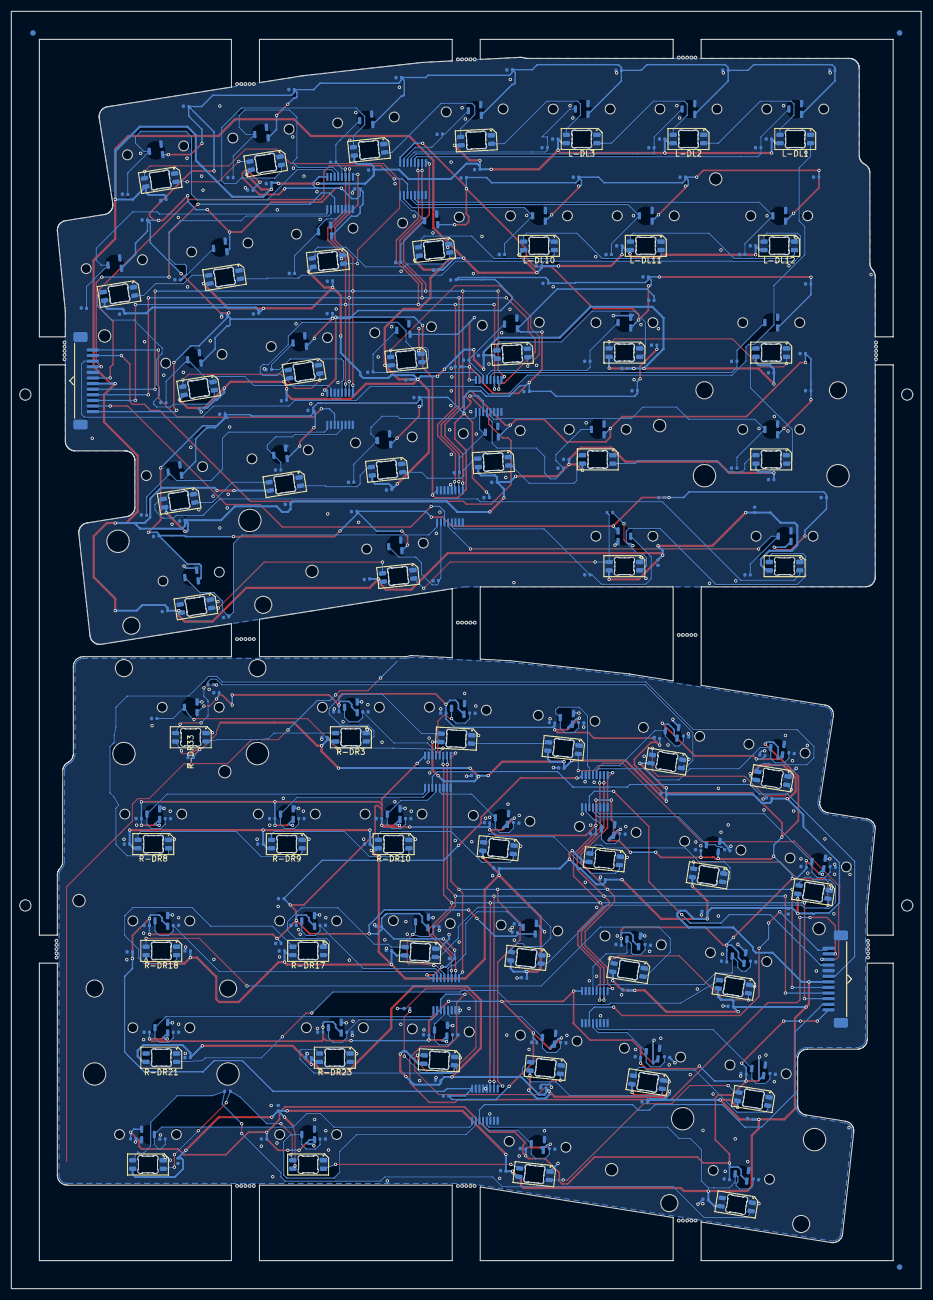
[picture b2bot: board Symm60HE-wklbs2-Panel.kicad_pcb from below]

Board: 2 copper layers, 162.3 x 227.8 mm, 406 parts (324 on the bottom side), 140 nets.

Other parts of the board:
FID1, FID2, FID3: FIDUCIAL_1MM_BCU; Fiducial_1mm_BCu
L-MHL1, L-MHL2, L-MHL3, L-MHL4: M2_NPTH; MountingHole_2.2mm_M2_NPTH
L-SL1, L-SL2: STAB_MX; STABILIZER_MX_2U
MB1, MB2, MB3, MB4, MB5, MB6, MB7, MB8, MB9, MB10, MB11, MB12, MB13, MB14, MB15, MB16, MB17, MB18, MB19, MB20, MB21, MB22, MB23, MB24, MB25, MB26, MB27, MB28, MB29, MB30, MB31, MB32, MB33, MB34, MB35, MB36, MB37, MB38, MB39, MB40, MB41, MB42, MB43, MB44, MB45, MB46, MB47, MB48, MB49, MB50, MB51, MB52, MB53, MB54, MB55, MB56, MB57, MB58, MB59, MB60, MB61, MB62, MB63, MB64, MB65: MOUSE_BITE_0.5MM; MouseBite_0.5mm
R-MHR1, R-MHR2, R-MHR3, R-MHR4: M2_NPTH; MountingHole_2.2mm_M2_NPTH
R-SR1, R-SR2, R-SR3: STAB_MX; STABILIZER_MX_2U
TH1, TH2, TH3, TH4: TOOLING_HOLE_2MM; ToolingHole_2mm_NPTH

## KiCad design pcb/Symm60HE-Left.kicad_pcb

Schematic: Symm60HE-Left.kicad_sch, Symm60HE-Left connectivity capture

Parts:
AML1, AML2, AML3, AML4, AML5: SN74LV4051A
CL1A, CL2A, CL3A, CL4A, CL5A, CL6A, CL7A, CL8A, CL9A, CL10A, CL11A, CL12A, CL13A, CL14A, CL15A, CL16A, CL17A, CL18A, CL19A, CL20A, CL21A, CL22A, CL23A, CL24A, CL25A, CL26A, CL27A, CL28A, CL29A, CL30A, CL31A, CL32A, CL33A: 100n
CL1B, CL2B, CL3B, CL4B, CL5B, CL6B, CL7B, CL8B, CL9B, CL10B, CL11B, CL12B, CL13B, CL14B, CL15B, CL16B, CL17B, CL18B, CL19B, CL20B, CL21B, CL22B, CL23B, CL24B, CL25B, CL26B, CL27B, CL28B, CL29B, CL30B, CL31B, CL32B, CL33B: 4.7n
CML1, CML2, CML3, CML4, CML5: 100n
CRGBL1, CRGBL2, CRGBL3, CRGBL4, CRGBL5, CRGBL6, CRGBL7, CRGBL8, CRGBL9, CRGBL10, CRGBL11, CRGBL12, CRGBL13, CRGBL14, CRGBL15, CRGBL16, CRGBL17, CRGBL18, CRGBL19, CRGBL20, CRGBL21, CRGBL22, CRGBL23, CRGBL24, CRGBL25, CRGBL26, CRGBL27, CRGBL29, CRGBL30, CRGBL31, CRGBL33: 100n
DL1, DL2, DL3, DL4, DL5, DL6, DL7, DL8, DL9, DL10, DL11, DL12, DL13, DL14, DL15, DL16, DL17, DL18, DL19, DL20, DL21, DL22, DL23, DL24, DL25, DL26, DL27, DL29, DL30, DL31, DL33: SK6812MINI-E
HEL1, HEL2, HEL3, HEL4, HEL5, HEL6, HEL7, HEL8, HEL9, HEL10, HEL11, HEL12, HEL13, HEL14, HEL15, HEL16, HEL17, HEL18, HEL19, HEL20, HEL21, HEL22, HEL23, HEL24, HEL25, HEL26, HEL27, HEL28, HEL29, HEL30, HEL31, HEL32, HEL33: MT9102ET
JL1: FFC_12P
RBPL29: 0R_DNP

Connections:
+3V3A: AML1.16 (+3V3A), AML2.16 (+3V3A), AML3.16 (+3V3A), AML4.16 (+3V3A), AML5.16 (+3V3A), CL1A.1 (+3V3A), CL2A.1 (+3V3A), CL3A.1 (+3V3A), CL4A.1 (+3V3A), CL5A.1 (+3V3A), CL6A.1 (+3V3A), CL7A.1 (+3V3A), CL8A.1 (+3V3A), CL9A.1 (+3V3A), CL10A.1 (+3V3A), CL11A.1 (+3V3A), CL12A.1 (+3V3A), CL13A.1 (+3V3A), CL14A.1 (+3V3A), CL15A.1 (+3V3A), CL16A.1 (+3V3A), CL17A.1 (+3V3A), CL18A.1 (+3V3A), CL19A.1 (+3V3A), CL20A.1 (+3V3A), CL21A.1 (+3V3A), CL22A.1 (+3V3A), CL23A.1 (+3V3A), CL24A.1 (+3V3A), CL25A.1 (+3V3A), CL26A.1 (+3V3A), CL27A.1 (+3V3A), CL28A.1 (+3V3A), CL29A.1 (+3V3A), CL30A.1 (+3V3A), CL31A.1 (+3V3A), CL32A.1 (+3V3A), CL33A.1 (+3V3A), CML1.1 (+3V3A), CML2.1 (+3V3A), CML3.1 (+3V3A), CML4.1 (+3V3A), CML5.1 (+3V3A), HEL1.1 (+3V3A), HEL2.1 (+3V3A), HEL3.1 (+3V3A), HEL4.1 (+3V3A), HEL5.1 (+3V3A), HEL6.1 (+3V3A), HEL7.1 (+3V3A), HEL8.1 (+3V3A), HEL9.1 (+3V3A), HEL10.1 (+3V3A), HEL11.1 (+3V3A), HEL12.1 (+3V3A), HEL13.1 (+3V3A), HEL14.1 (+3V3A), HEL15.1 (+3V3A), HEL16.1 (+3V3A), HEL17.1 (+3V3A), HEL18.1 (+3V3A), HEL19.1 (+3V3A), HEL20.1 (+3V3A), HEL21.1 (+3V3A), HEL22.1 (+3V3A), HEL23.1 (+3V3A), HEL24.1 (+3V3A), HEL25.1 (+3V3A), HEL26.1 (+3V3A), HEL27.1 (+3V3A), HEL28.1 (+3V3A), HEL29.1 (+3V3A), HEL30.1 (+3V3A), HEL31.1 (+3V3A), HEL32.1 (+3V3A), HEL33.1 (+3V3A), JL1.12 (+3V3A)
ADC_L1: AML1.3 (ADC_L1), JL1.6 (ADC_L1)
ADC_L2: AML2.3 (ADC_L2), JL1.4 (ADC_L2)
ADC_L3: AML3.3 (ADC_L3), JL1.2 (ADC_L3)
ADC_L4: AML4.3 (ADC_L4), JL1.1 (ADC_L4)
ADC_L5: AML5.3 (ADC_L5), JL1.11 (ADC_L5)
GND: AML1.6 (GND), AML1.7 (GND), AML1.8 (GND), AML2.6 (GND), AML2.7 (GND), AML2.8 (GND), AML3.6 (GND), AML3.7 (GND), AML3.8 (GND), AML4.4 (GND), AML4.6 (GND), AML4.7 (GND), AML4.8 (GND), AML5.1 (GND), AML5.2 (GND), AML5.4 (GND), AML5.5 (GND), AML5.6 (GND), AML5.7 (GND), AML5.8 (GND), AML5.12 (GND), AML5.15 (GND), CL1A.2 (GND), CL1B.2 (GND), CL2A.2 (GND), CL2B.2 (GND), CL3A.2 (GND), CL3B.2 (GND), CL4A.2 (GND), CL4B.2 (GND), CL5A.2 (GND), CL5B.2 (GND), CL6A.2 (GND), CL6B.2 (GND), CL7A.2 (GND), CL7B.2 (GND), CL8A.2 (GND), CL8B.2 (GND), CL9A.2 (GND), CL9B.2 (GND), CL10A.2 (GND), CL10B.2 (GND), CL11A.2 (GND), CL11B.2 (GND), CL12A.2 (GND), CL12B.2 (GND), CL13A.2 (GND), CL13B.2 (GND), CL14A.2 (GND), CL14B.2 (GND), CL15A.2 (GND), CL15B.2 (GND), CL16A.2 (GND), CL16B.2 (GND), CL17A.2 (GND), CL17B.2 (GND), CL18A.2 (GND), CL18B.2 (GND), CL19A.2 (GND), CL19B.2 (GND), CL20A.2 (GND), CL20B.2 (GND), CL21A.2 (GND), CL21B.2 (GND), CL22A.2 (GND), CL22B.2 (GND), CL23A.2 (GND), CL23B.2 (GND), CL24A.2 (GND), CL24B.2 (GND), CL25A.2 (GND), CL25B.2 (GND), CL26A.2 (GND), CL26B.2 (GND), CL27A.2 (GND), CL27B.2 (GND), CL28A.2 (GND), CL28B.2 (GND), CL29A.2 (GND), CL29B.2 (GND), CL30A.2 (GND), CL30B.2 (GND), CL31A.2 (GND), CL31B.2 (GND), CL32A.2 (GND), CL32B.2 (GND), CL33A.2 (GND), CL33B.2 (GND), CML1.2 (GND), CML2.2 (GND), CML3.2 (GND), CML4.2 (GND), CML5.2 (GND), CRGBL1.2 (GND), CRGBL2.2 (GND), CRGBL3.2 (GND), CRGBL4.2 (GND), CRGBL5.2 (GND), CRGBL6.2 (GND), CRGBL7.2 (GND), CRGBL8.2 (GND), CRGBL9.2 (GND)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
HE_L01: AML1.13 (HE_L01), CL1B.1 (HE_L01), HEL1.3 (HE_L01)
HE_L02: AML1.14 (HE_L02), CL2B.1 (HE_L02), HEL2.3 (HE_L02)
HE_L03: AML1.15 (HE_L03), CL3B.1 (HE_L03), HEL3.3 (HE_L03)
HE_L04: AML1.12 (HE_L04), CL4B.1 (HE_L04), HEL4.3 (HE_L04)
HE_L05: AML1.1 (HE_L05), CL5B.1 (HE_L05), HEL5.3 (HE_L05)
HE_L06: AML1.5 (HE_L06), CL6B.1 (HE_L06), HEL6.3 (HE_L06)
HE_L07: AML1.2 (HE_L07), CL7B.1 (HE_L07), HEL7.3 (HE_L07)
HE_L08: AML1.4 (HE_L08), CL8B.1 (HE_L08), HEL8.3 (HE_L08)
HE_L09: AML2.13 (HE_L09), CL9B.1 (HE_L09), HEL9.3 (HE_L09)
HE_L10: AML2.14 (HE_L10), CL10B.1 (HE_L10), HEL10.3 (HE_L10)
HE_L11: AML2.15 (HE_L11), CL11B.1 (HE_L11), HEL11.3 (HE_L11)
HE_L12: AML2.12 (HE_L12), CL12B.1 (HE_L12), HEL12.3 (HE_L12)
HE_L13: AML2.1 (HE_L13), CL13B.1 (HE_L13), HEL13.3 (HE_L13)
HE_L14: AML2.5 (HE_L14), CL14B.1 (HE_L14), HEL14.3 (HE_L14)
HE_L15: AML2.2 (HE_L15), CL15B.1 (HE_L15), HEL15.3 (HE_L15)
HE_L16: AML2.4 (HE_L16), CL16B.1 (HE_L16), HEL16.3 (HE_L16)
HE_L17: AML3.13 (HE_L17), CL17B.1 (HE_L17), HEL17.3 (HE_L17)
HE_L18: AML3.14 (HE_L18), CL18B.1 (HE_L18), HEL18.3 (HE_L18)
HE_L19: AML3.15 (HE_L19), CL19B.1 (HE_L19), HEL19.3 (HE_L19)
HE_L20: AML3.12 (HE_L20), CL20B.1 (HE_L20), HEL20.3 (HE_L20)
HE_L21: AML3.1 (HE_L21), CL21B.1 (HE_L21), HEL21.3 (HE_L21)
HE_L22: AML3.5 (HE_L22), CL22B.1 (HE_L22), HEL22.3 (HE_L22)
HE_L23: AML3.2 (HE_L23), CL23B.1 (HE_L23), HEL23.3 (HE_L23)
HE_L24: AML3.4 (HE_L24), CL24B.1 (HE_L24), HEL24.3 (HE_L24)
HE_L25: AML4.13 (HE_L25), CL25B.1 (HE_L25), HEL25.3 (HE_L25)
HE_L26: AML4.14 (HE_L26), CL26B.1 (HE_L26), HEL26.3 (HE_L26)
HE_L27: AML4.15 (HE_L27), CL27B.1 (HE_L27), HEL27.3 (HE_L27)
HE_L28: AML4.12 (HE_L28), CL29B.1 (HE_L28), HEL29.3 (HE_L28)
HE_L29: AML4.1 (HE_L29), CL31B.1 (HE_L29), HEL31.3 (HE_L29)
HE_L30: AML4.5 (HE_L30), CL32B.1 (HE_L30), HEL32.3 (HE_L30)
HE_L31: AML4.2 (HE_L31), CL33B.1 (HE_L31), HEL33.3 (HE_L31)
HE_L32: AML5.13 (HE_L32), CL28B.1 (HE_L32), HEL28.3 (HE_L32)
HE_L33: AML5.14 (HE_L33), CL30B.1 (HE_L33), HEL30.3 (HE_L33)
MUX_A0: AML1.11 (MUX_A0), AML2.11 (MUX_A0), AML3.11 (MUX_A0), AML4.11 (MUX_A0), AML5.11 (MUX_A0), JL1.10 (MUX_A0)
MUX_A1: AML1.10 (MUX_A1), AML2.10 (MUX_A1), AML3.10 (MUX_A1), AML4.10 (MUX_A1), AML5.10 (MUX_A1), JL1.9 (MUX_A1)
MUX_A2: AML1.9 (MUX_A2), AML2.9 (MUX_A2), AML3.9 (MUX_A2), AML4.9 (MUX_A2), AML5.9 (MUX_A2), JL1.8 (MUX_A2)
RGB_L: DL1.2 (RGB_L), JL1.3 (RGB_L)
RGB_L_01: DL1.4 (RGB_L_01), DL2.2 (RGB_L_01)
RGB_L_02: DL2.4 (RGB_L_02), DL3.2 (RGB_L_02)
RGB_L_03: DL3.4 (RGB_L_03), DL4.2 (RGB_L_03)
RGB_L_04: DL4.4 (RGB_L_04), DL5.2 (RGB_L_04)
RGB_L_05: DL5.4 (RGB_L_05), DL6.2 (RGB_L_05)
RGB_L_06: DL6.4 (RGB_L_06), DL7.2 (RGB_L_06)
RGB_L_07: DL7.4 (RGB_L_07), DL8.2 (RGB_L_07)
RGB_L_08: DL8.4 (RGB_L_08), DL9.2 (RGB_L_08)
RGB_L_09: DL9.4 (RGB_L_09), DL10.2 (RGB_L_09)
RGB_L_10: DL10.4 (RGB_L_10), DL11.2 (RGB_L_10)
RGB_L_11: DL11.4 (RGB_L_11), DL12.2 (RGB_L_11)
RGB_L_12: DL12.4 (RGB_L_12), DL13.2 (RGB_L_12)
RGB_L_13: DL13.4 (RGB_L_13), DL14.2 (RGB_L_13)
RGB_L_14: DL14.4 (RGB_L_14), DL15.2 (RGB_L_14)
RGB_L_15: DL15.4 (RGB_L_15), DL16.2 (RGB_L_15)
RGB_L_16: DL16.4 (RGB_L_16), DL17.2 (RGB_L_16)
RGB_L_17: DL17.4 (RGB_L_17), DL18.2 (RGB_L_17)
RGB_L_18: DL18.4 (RGB_L_18), DL19.2 (RGB_L_18)
RGB_L_19: DL19.4 (RGB_L_19), DL20.2 (RGB_L_19)
RGB_L_20: DL20.4 (RGB_L_20), DL21.2 (RGB_L_20)
RGB_L_21: DL21.4 (RGB_L_21), DL22.2 (RGB_L_21)
RGB_L_22: DL22.4 (RGB_L_22), DL23.2 (RGB_L_22)
RGB_L_23: DL23.4 (RGB_L_23), DL24.2 (RGB_L_23)
RGB_L_24: DL24.4 (RGB_L_24), DL25.2 (RGB_L_24)
RGB_L_25: DL25.4 (RGB_L_25), DL26.2 (RGB_L_25)
RGB_L_26: DL26.4 (RGB_L_26), DL27.2 (RGB_L_26)
RGB_L_27: DL27.4 (RGB_L_27), DL33.2 (RGB_L_27)
RGB_L_28: DL29.2 (RGB_L_28), DL33.4 (RGB_L_28), RBPL29.1 (RGB_L_28)
RGB_L_29: DL29.4 (RGB_L_29), DL30.2 (RGB_L_29), RBPL29.2 (RGB_L_29)
RGB_L_30: DL30.4 (RGB_L_30), DL31.2 (RGB_L_30)
RGB_L_END: DL31.4 (RGB_L_END)
VBUS: CRGBL1.1 (VBUS), CRGBL2.1 (VBUS), CRGBL3.1 (VBUS), CRGBL4.1 (VBUS), CRGBL5.1 (VBUS), CRGBL6.1 (VBUS), CRGBL7.1 (VBUS), CRGBL8.1 (VBUS), CRGBL9.1 (VBUS), CRGBL10.1 (VBUS), CRGBL11.1 (VBUS), CRGBL12.1 (VBUS), CRGBL13.1 (VBUS), CRGBL14.1 (VBUS), CRGBL15.1 (VBUS), CRGBL16.1 (VBUS), CRGBL17.1 (VBUS), CRGBL18.1 (VBUS), CRGBL19.1 (VBUS), CRGBL20.1 (VBUS), CRGBL21.1 (VBUS), CRGBL22.1 (VBUS), CRGBL23.1 (VBUS), CRGBL24.1 (VBUS), CRGBL25.1 (VBUS), CRGBL26.1 (VBUS), CRGBL27.1 (VBUS), CRGBL29.1 (VBUS), CRGBL30.1 (VBUS), CRGBL31.1 (VBUS), CRGBL33.1 (VBUS), DL1.3 (VBUS), DL2.3 (VBUS), DL3.3 (VBUS), DL4.3 (VBUS), DL5.3 (VBUS), DL6.3 (VBUS), DL7.3 (VBUS), DL8.3 (VBUS), DL9.3 (VBUS), DL10.3 (VBUS), DL11.3 (VBUS), DL12.3 (VBUS), DL13.3 (VBUS), DL14.3 (VBUS), DL15.3 (VBUS), DL16.3 (VBUS), DL17.3 (VBUS), DL18.3 (VBUS), DL19.3 (VBUS), DL20.3 (VBUS), DL21.3 (VBUS), DL22.3 (VBUS), DL23.3 (VBUS), DL24.3 (VBUS), DL25.3 (VBUS), DL26.3 (VBUS), DL27.3 (VBUS), DL29.3 (VBUS), DL30.3 (VBUS), DL31.3 (VBUS), DL33.3 (VBUS), JL1.7 (VBUS)

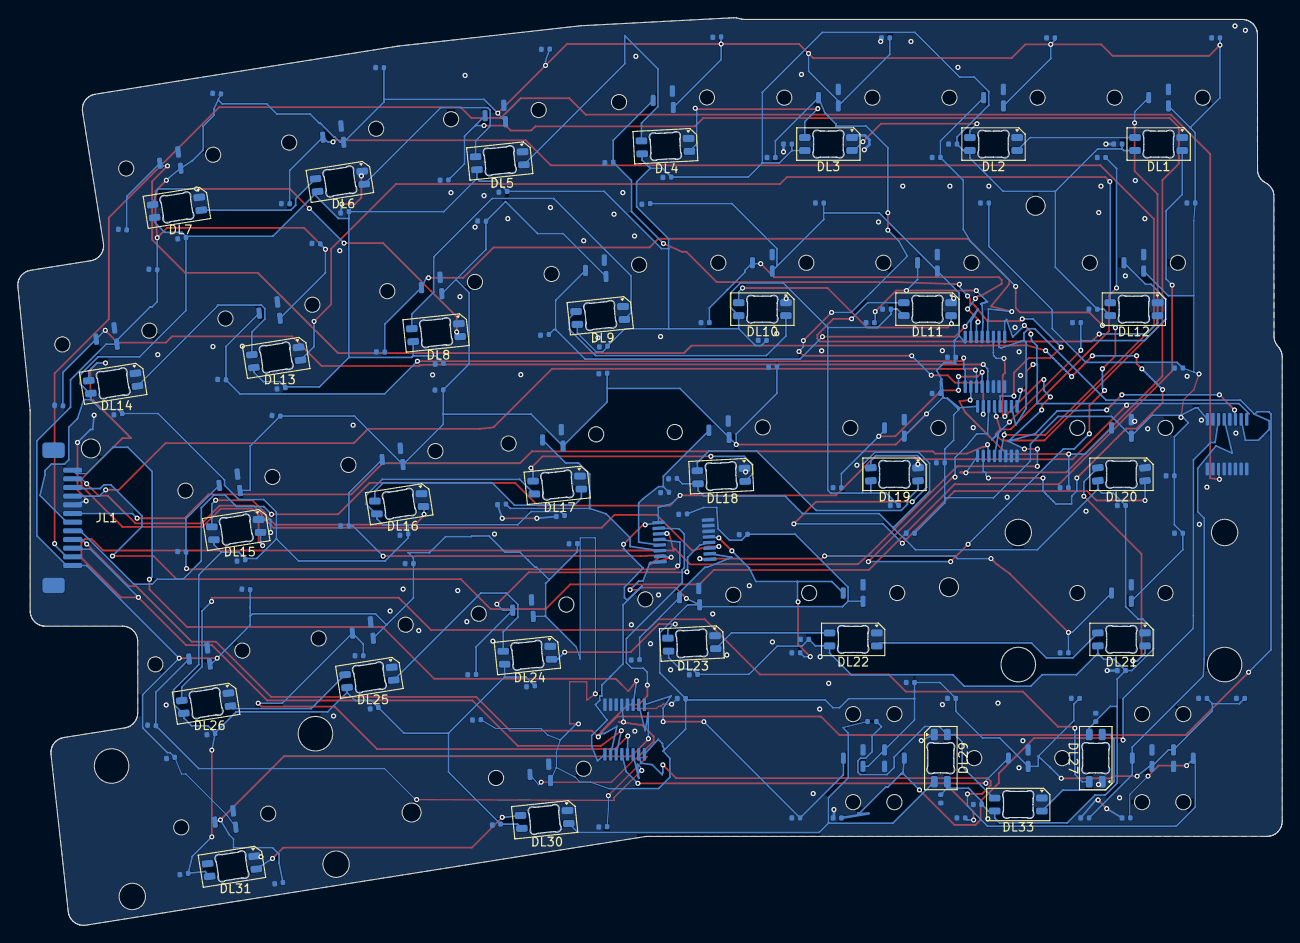
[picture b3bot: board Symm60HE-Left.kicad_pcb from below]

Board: 2 copper layers, 145.9 x 104.7 mm, 179 parts (173 on the bottom side), 75 nets.

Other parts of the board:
MHL1, MHL2, MHL3, MHL4: M2_NPTH; MountingHole_2.2mm_M2_NPTH
SL1, SL2: STAB_MX; STABILIZER_MX_2U
